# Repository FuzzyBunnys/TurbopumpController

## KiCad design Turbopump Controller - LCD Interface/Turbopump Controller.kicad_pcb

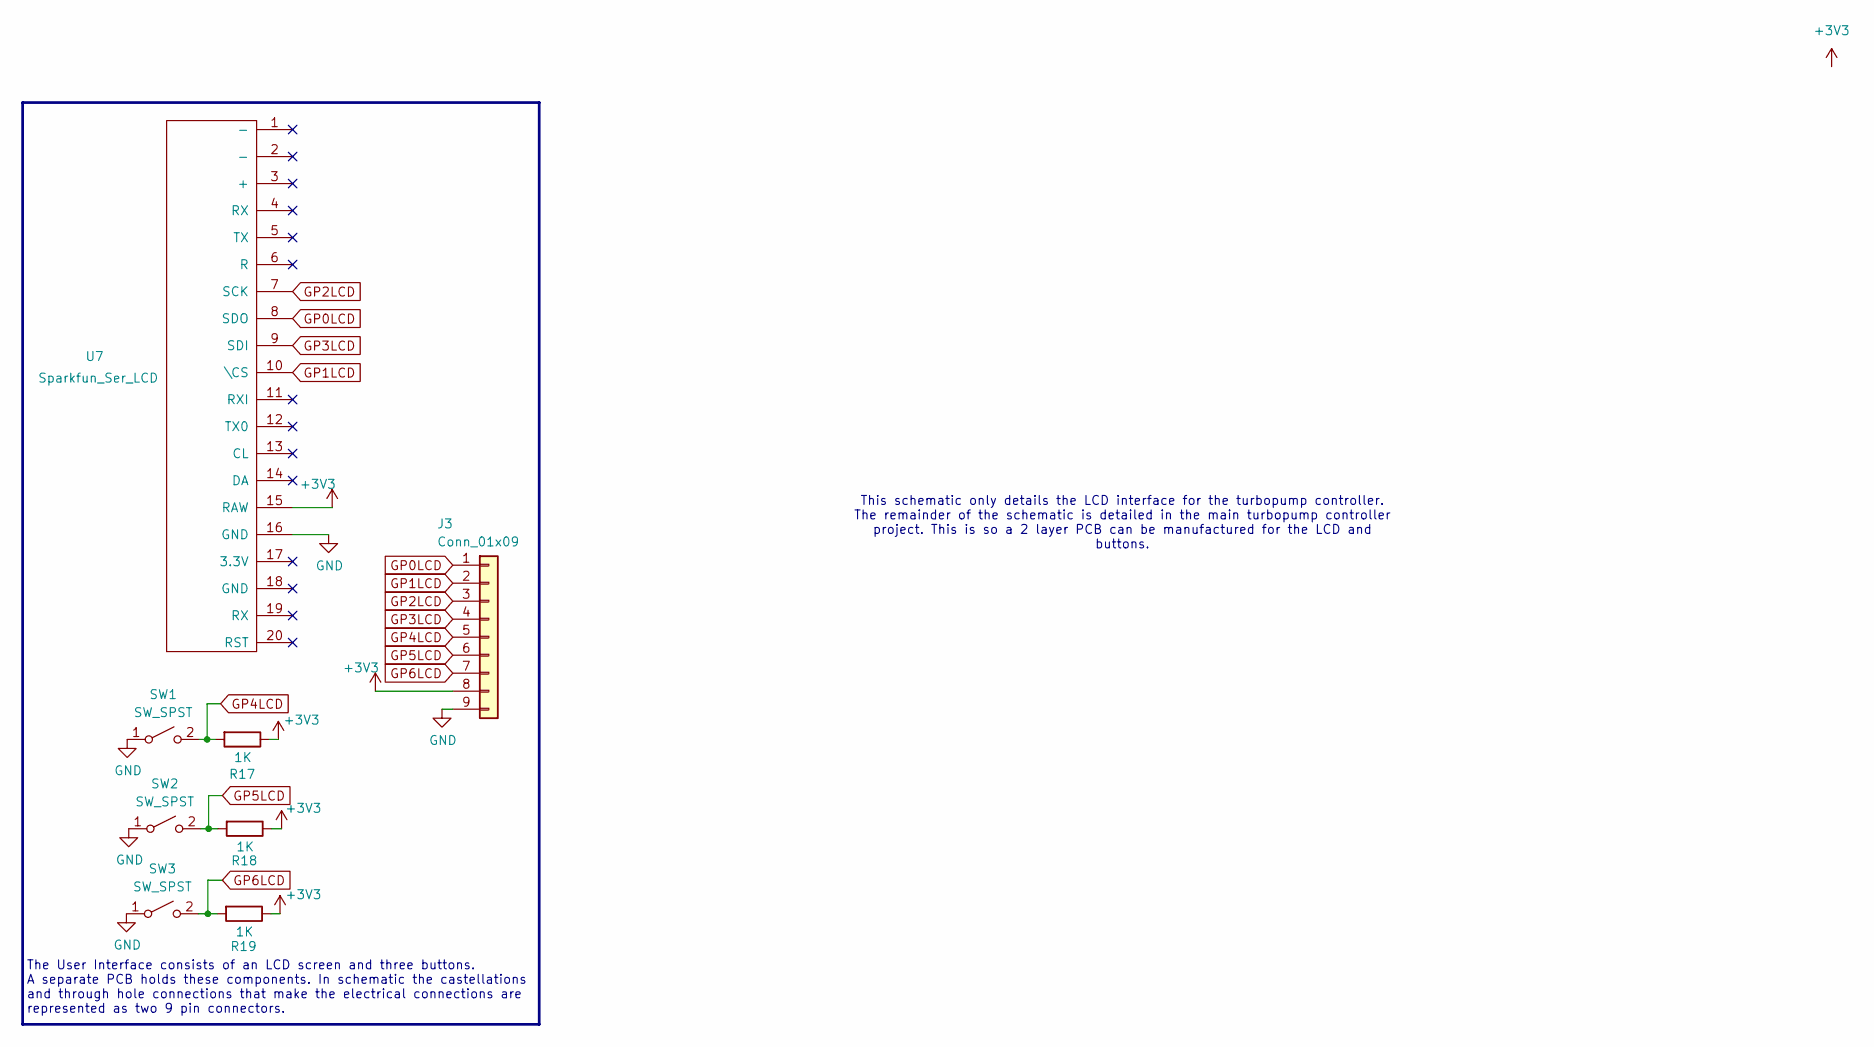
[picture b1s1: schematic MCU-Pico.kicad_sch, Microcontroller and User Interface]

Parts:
J3: Conn_01x09; Castellated_Tpump_Connector
R17, R18, R19: 1K; R_0603_1608Metric
SW1, SW2, SW3: SW_SPST; TL2233 Series Pushbutton Switch
U7: Sparkfun_Ser_LCD; LCD-16X2

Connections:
+3V3: J3.8, R17.1, R18.1, R19.1, U7.15 (RAW)
GND: J3.9, SW1.1 (A), SW2.1 (A), SW3.1 (A), U7.16 (GND)
GP0LCD: J3.1, U7.8 (SDO)
GP1LCD: J3.2, U7.10 (\CS)
GP2LCD: J3.3, U7.7 (SCK)
GP3LCD: J3.4, U7.9 (SDI)
GP4LCD: J3.5, R17.2, SW1.2 (B)
GP5LCD: J3.6, R18.2, SW2.2 (B)
GP6LCD: J3.7, R19.2, SW3.2 (B)

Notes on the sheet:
This schematic only details the LCD interface for the turbopump controller. The remainder of the schematic is detailed in the main turbopump controller project. This is so a 2 layer PCB can be manufactured for the LCD and buttons.
The User Interface consists of an LCD screen and three buttons. A separate PCB holds these components. In schematic the castellations and through hole connections that make the electrical connections are represented as two 9 pin connectors.

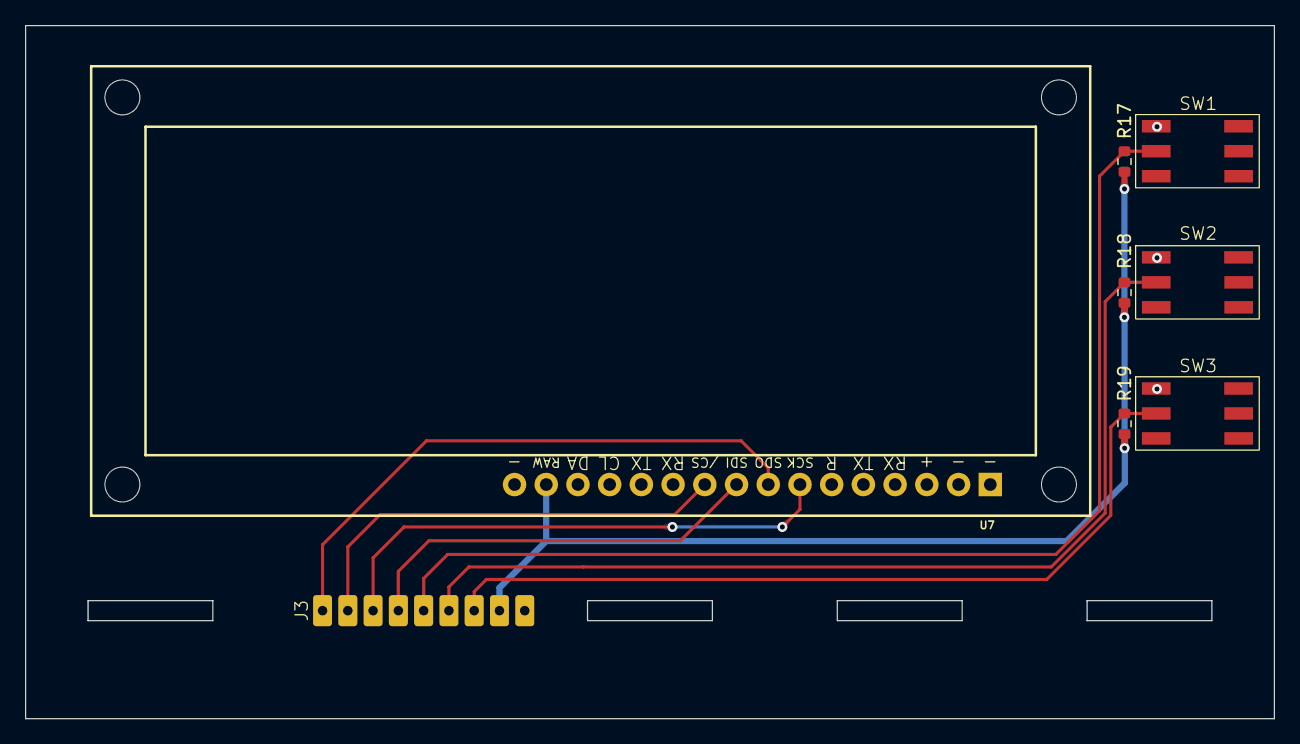
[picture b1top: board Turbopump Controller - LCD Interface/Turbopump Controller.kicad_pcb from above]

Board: 2 copper layers, 100.0 x 55.5 mm, 8 parts (0 on the bottom side), 9 nets.

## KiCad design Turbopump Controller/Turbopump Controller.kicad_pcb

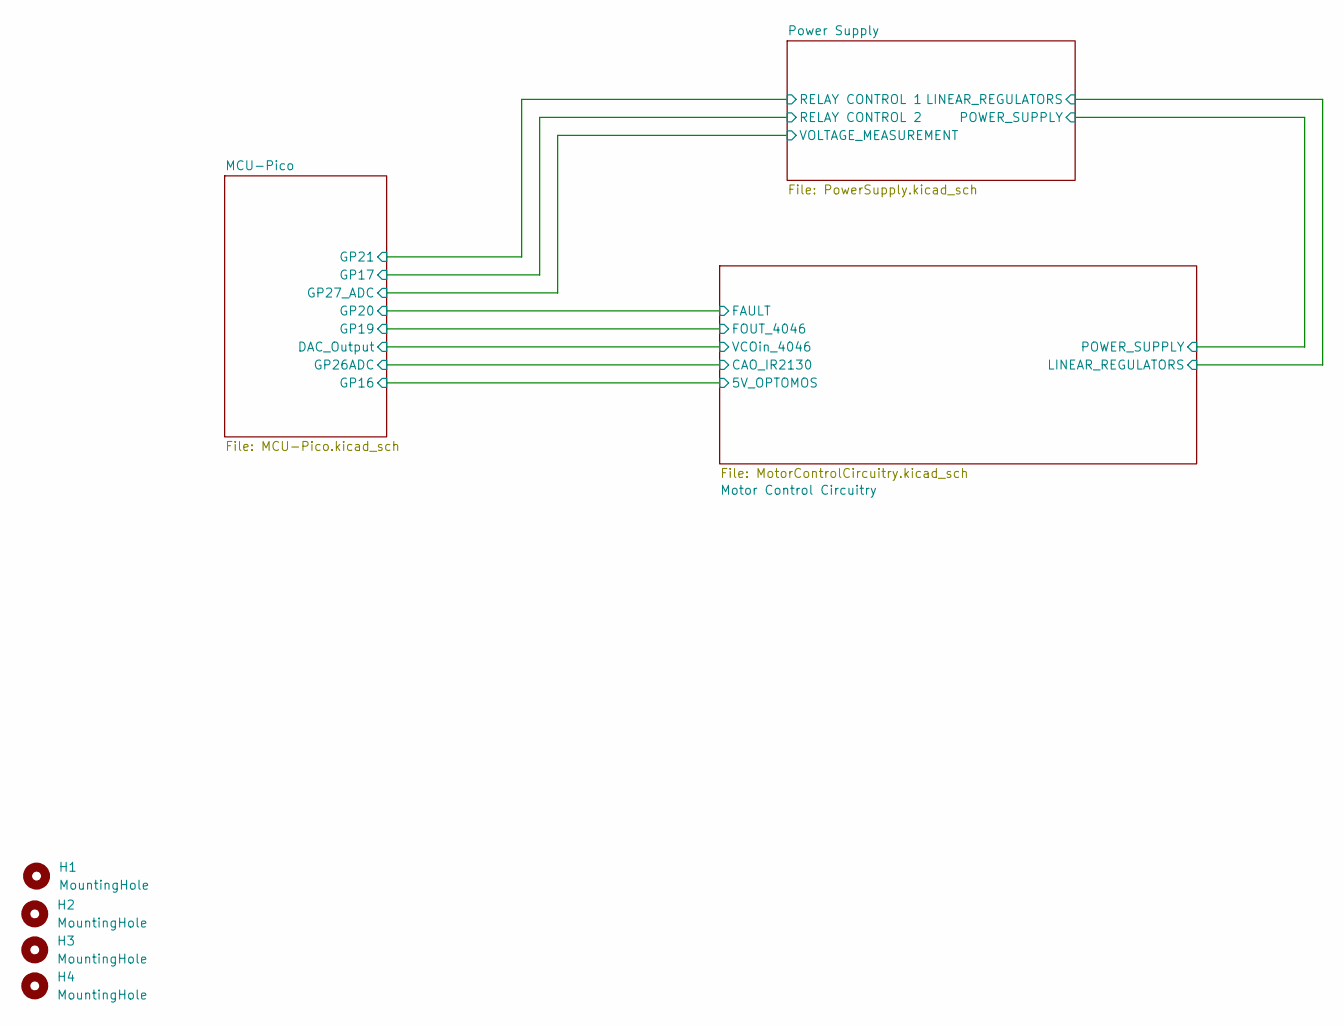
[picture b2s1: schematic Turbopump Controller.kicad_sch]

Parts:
H1, H2, H4: MountingHole; MountingHole_3.2mm_M3_Pad_Via
H3: MountingHole; MountingHole_2.2mm_M2_Pad_Via

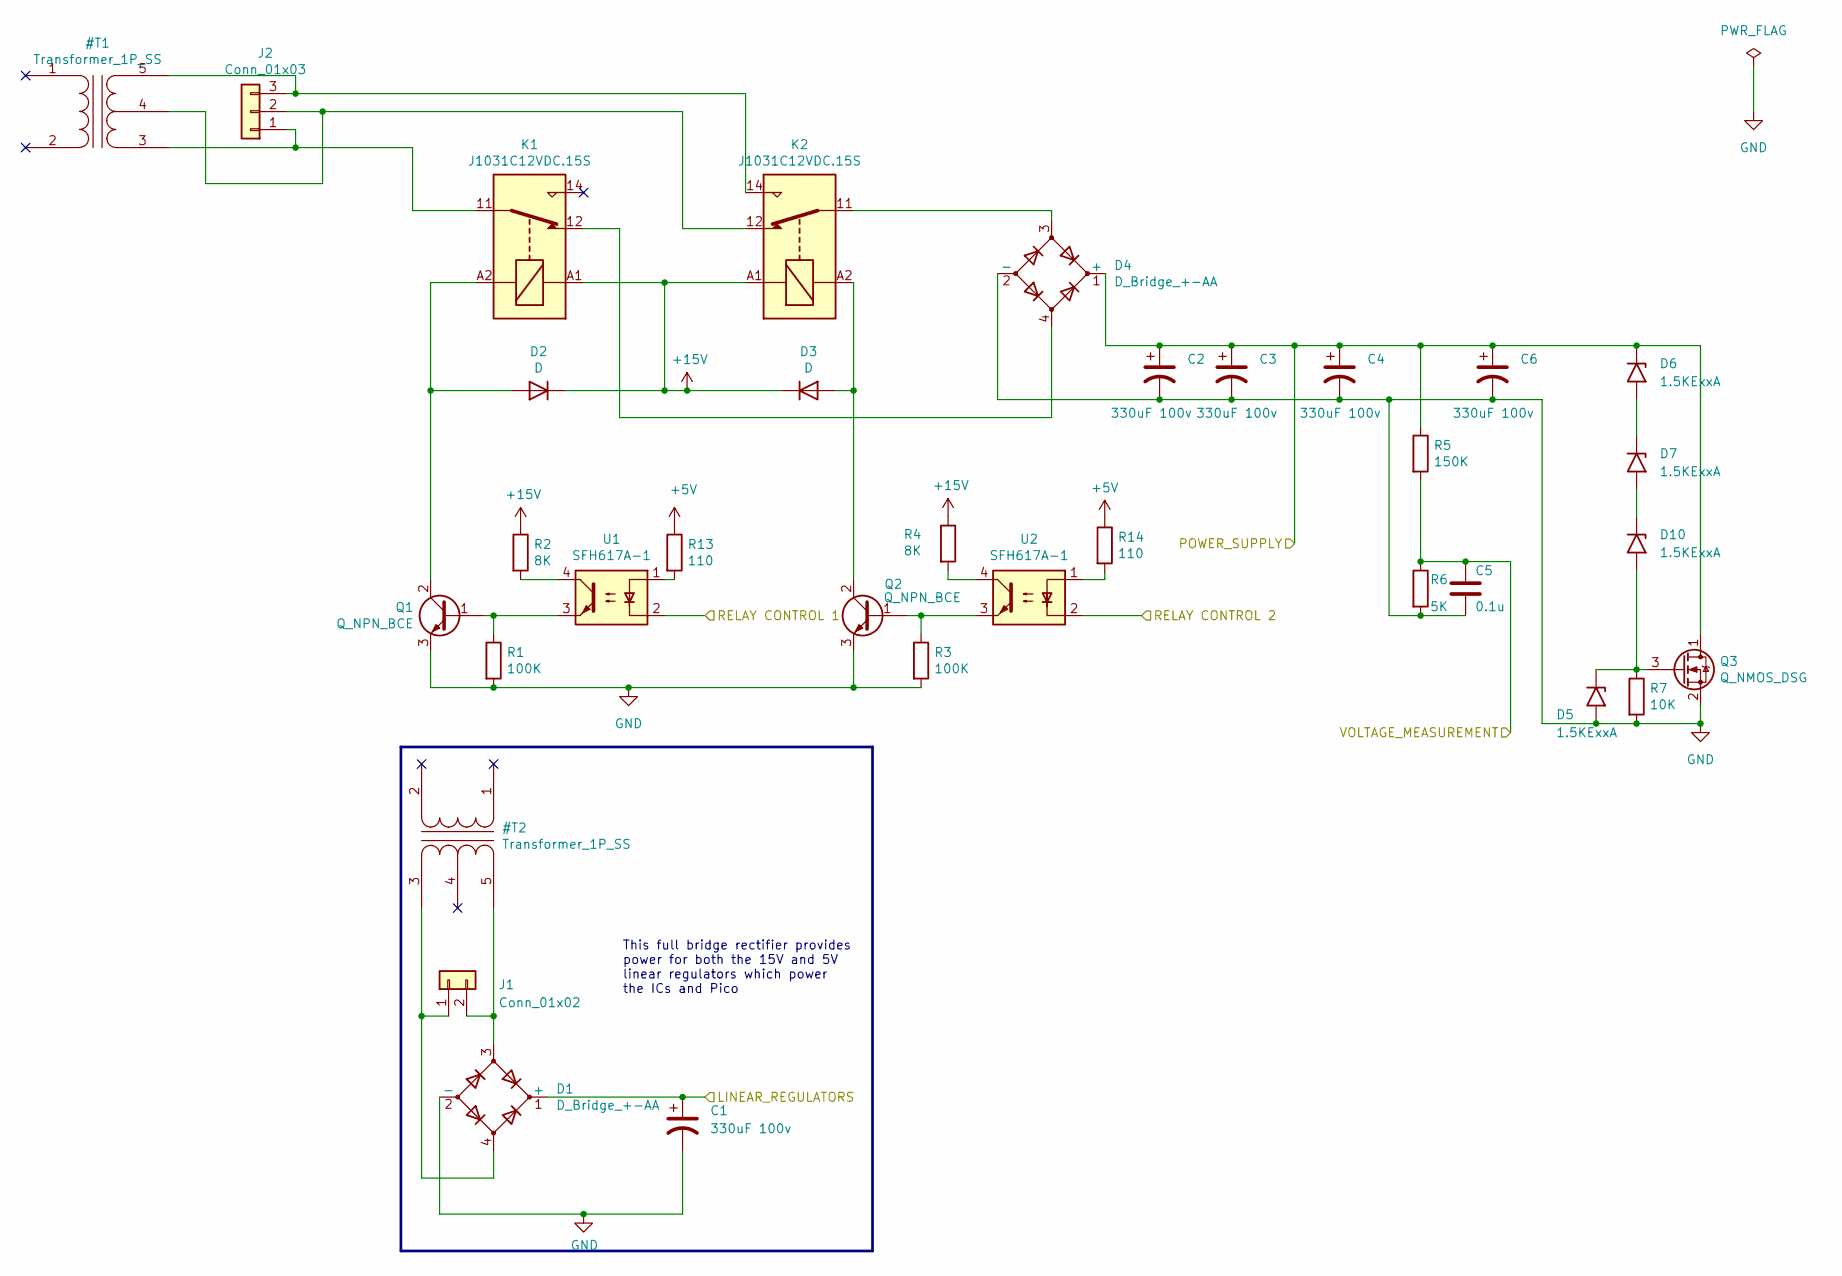
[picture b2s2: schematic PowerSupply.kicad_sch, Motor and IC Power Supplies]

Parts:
C1, C2, C3, C4, C6: 330uF 100v; EEV-FK2A331M
C5: 0.1u; C_0603_1608Metric
D1: D_Bridge_+-AA; KMB25S
D2, D3: D; D_SOD-323F
D4: D_Bridge_+-AA; RDBF32-13
D5, D10: 1.5KExxA; D_SMC_Modified
D6, D7: 1.5KExxA; D_SMB_Modified
J1: Conn_01x02; TerminalBlock_bornier-2_P5.08mm
J2: Conn_01x03; TerminalBlock_bornier-3_P5.08mm
K1, K2: J1031C12VDC.15S; Relay_SPDT_HsinDa_Y14
Q1, Q2: Q_NPN_BCE; SOT-23
Q3: Q_NMOS_DSG; DMTH10H003SPSW-13
R1, R3: 100K; R_0603_1608Metric
R2, R4: 8K; R_0603_1608Metric
R5: 150K; R_0805_2012Metric
R6: 5K; R_0805_2012Metric
R7: 10K; R_0805_2012Metric
R13, R14: 110; R_0603_1608Metric
U1, U2: SFH617A-1; 4-SMD Gullwing

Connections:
+5V: R13.1, R14.1; also elsewhere on the board
+15V: D2.1 (K), D3.1 (K), K1.A1, K2.A1, R2.1, R4.1; also elsewhere on the board
/MCU-Pico/GP17: U2.2; also elsewhere on the board
/MCU-Pico/GP21: U1.2; also elsewhere on the board
/MCU-Pico/GP27_ADC: C5.1, R5.2, R6.1; also elsewhere on the board
/Motor Control Circuitry/LINEAR_REGULATORS: C1.1, D1.1 (+); also elsewhere on the board
/Motor Control Circuitry/POWER_SUPPLY: C2.1, C3.1, C4.1, C6.1, D4.1 (+), D6.1 (A1), Q3.1 (D), R5.1; also elsewhere on the board
GND: C1.2, C2.2, C3.2, C4.2, C5.2, C6.2, D1.2 (-), D4.2 (-), D5.2 (A2), Q1.3 (E), Q2.3 (E), Q3.2 (S), R1.2, R3.2, R6.2, R7.2; also elsewhere on the board
unnamed: D2.2 (A), K1.A2, Q1.2 (C)
unnamed: D3.2 (A), K2.A2, Q2.2 (C)
unnamed: D4.3, K2.11
unnamed: D4.4, K1.12
unnamed: D6.2 (A2), D7.1 (A1)
unnamed: D7.2 (A2), D10.1 (A1)
unnamed: D5.1 (A1), D10.2 (A2), Q3.3 (G), R7.1
unnamed: Q1.1 (B), R1.1, U1.3
unnamed: Q2.1 (B), R3.1, U2.3
unnamed: R2.2, U1.4
unnamed: R4.2, U2.4
unnamed: R13.2, U1.1
unnamed: R14.2, U2.1

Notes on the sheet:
This full bridge rectifier provides power for both the 15V and 5V linear regulators which power the ICs and Pico

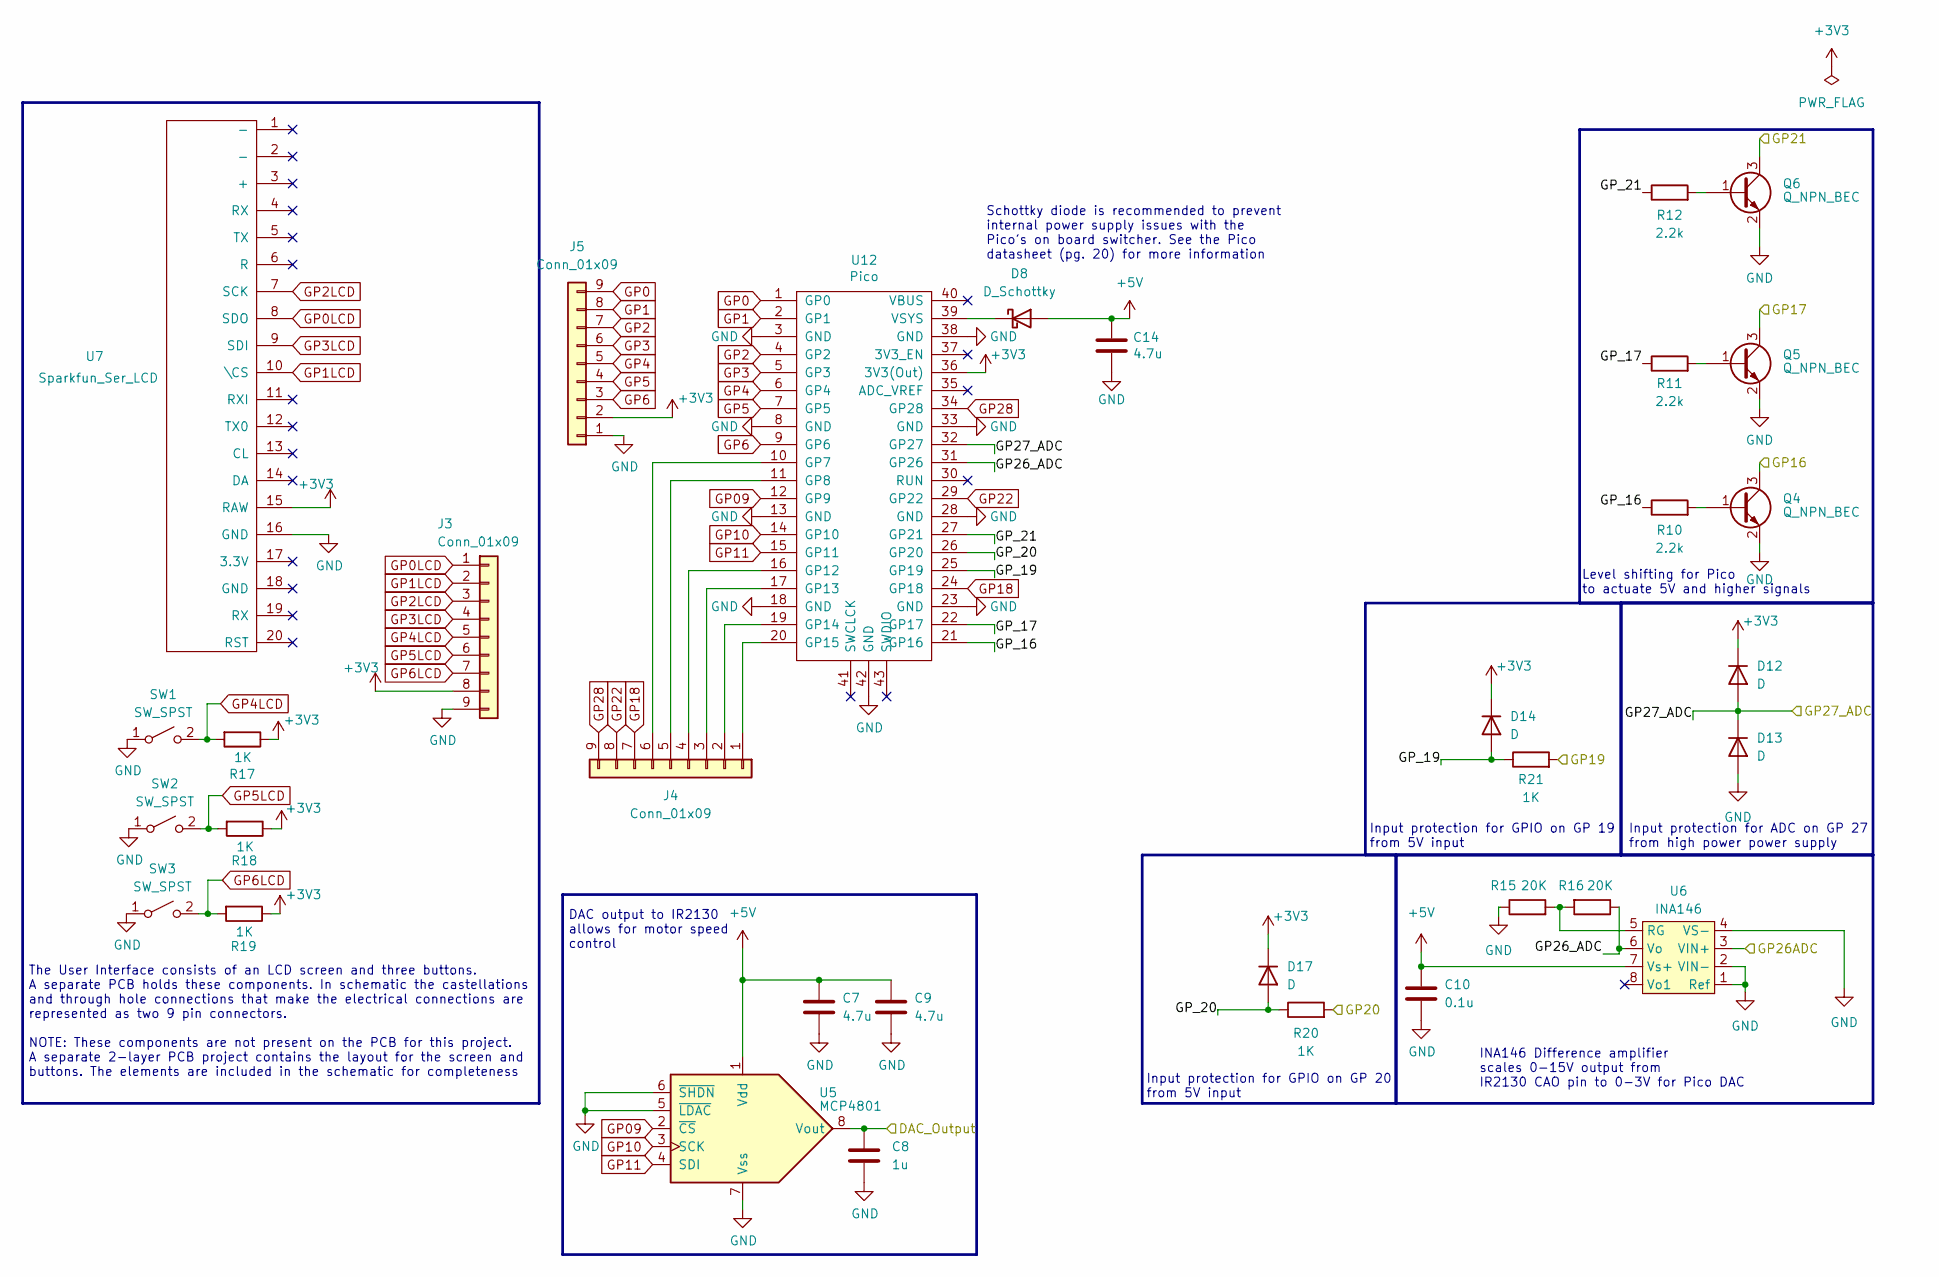
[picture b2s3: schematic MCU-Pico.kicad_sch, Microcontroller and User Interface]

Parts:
C7, C9, C14: 4.7u; C_0603_1608Metric
C8: 1u; C_0603_1608Metric
C10: 0.1u; C_0603_1608Metric
D8: D_Schottky; D_SOD-123F
D12, D13, D14, D17: D; D_SOD-882
J3, J5: Conn_01x09; Castellated_Tpump_Connector
J4: Conn_01x09; PinSocket_1x09_P2.54mm_Vertical
Q4, Q5, Q6: Q_NPN_BEC; TSOT-23
R10, R11, R12: 2.2k; R_0603_1608Metric
R15, R16: 20K; R_0603_1608Metric
R17, R18, R19, R20, R21: 1K; R_0603_1608Metric
SW1, SW2, SW3: SW_SPST; TL2233 Series Pushbutton Switch
U5: MCP4801; DFN-8-1EP_3x2mm_P0.5mm_EP1.75x1.45mm
U6: INA146; SOIC-8-1EP_3.9x4.9mm_P1.27mm_EP2.29x3mm
U7: Sparkfun_Ser_LCD; LCD-16X2
U12: Pico; RPi_Pico_SMD_TH

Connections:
+3V3: D12.1 (K), D14.1 (K), D17.1 (K), J3.8, J5.2, R17.1, R18.1, R19.1, U7.15 (RAW), U12.36 (3V3(Out))
+5V: C7.1, C9.1, C10.1, C14.1, D8.2 (A), U5.1 (Vdd), U6.7 (Vs+); also elsewhere on the board
/MCU-Pico/DAC_Output: C8.1, U5.8 (Vout); also elsewhere on the board
/MCU-Pico/GP16: Q4.3 (C); also elsewhere on the board
/MCU-Pico/GP17: Q5.3 (C); also elsewhere on the board
/MCU-Pico/GP19: R21.2; also elsewhere on the board
/MCU-Pico/GP20: R20.2; also elsewhere on the board
/MCU-Pico/GP21: Q6.3 (C); also elsewhere on the board
/MCU-Pico/GP26ADC: U6.3 (VIN+); also elsewhere on the board
/MCU-Pico/GP26_ADC: R16.1, U6.6 (Vo), U12.31 (GP26)
/MCU-Pico/GP27_ADC: D12.2 (A), D13.1 (K), U12.32 (GP27); also elsewhere on the board
/MCU-Pico/GP_16: R10.1, U12.21 (GP16)
/MCU-Pico/GP_17: R11.1, U12.22 (GP17)
/MCU-Pico/GP_19: D14.2 (A), R21.1, U12.25 (GP19)
/MCU-Pico/GP_20: D17.2 (A), R20.1, U12.26 (GP20)
/MCU-Pico/GP_21: R12.1, U12.27 (GP21)
GND: C7.2, C8.2, C9.2, C10.2, C14.2, D13.2 (A), J3.9, J5.1, Q4.2 (E), Q5.2 (E), Q6.2 (E), R15.1, SW1.1 (A), SW2.1 (A), SW3.1 (A), U5.5 (~LDAC), U5.6 (~SHDN), U5.7 (Vss), U6.1 (Ref), U6.2 (VIN-), U6.4 (VS-), U7.16 (GND), U12.3 (GND), U12.8 (GND), U12.13 (GND), U12.18 (GND), U12.23 (GND), U12.28 (GND), U12.33 (GND), U12.38 (GND), U12.42 (GND); also elsewhere on the board
GP0: J5.9, U12.1 (GP0)
GP1: J5.8, U12.2 (GP1)
GP2: J5.7, U12.4 (GP2)
GP3: J5.6, U12.5 (GP3)
GP4: J5.5, U12.6 (GP4)
GP5: J5.4, U12.7 (GP5)
GP6: J5.3, U12.9 (GP6)
GP09: U5.2 (~CS), U12.12 (GP9)
GP10: U5.3 (SCK), U12.14 (GP10)
GP11: U5.4 (SDI), U12.15 (GP11)
GP18: J4.7, U12.24 (GP18)
GP22: J4.8, U12.29 (GP22)
GP28: J4.9, U12.34 (GP28)
unnamed: D8.1 (K), U12.39 (VSYS)
unnamed: J3.1, U7.8 (SDO)
unnamed: J3.2, U7.10 (\CS)
unnamed: J3.3, U7.7 (SCK)
unnamed: J3.4, U7.9 (SDI)
unnamed: J3.5, R17.2, SW1.2 (B)
unnamed: J3.6, R18.2, SW2.2 (B)
unnamed: J3.7, R19.2, SW3.2 (B)
unnamed: J4.1, U12.20 (GP15)
unnamed: J4.2, U12.19 (GP14)
unnamed: J4.3, U12.17 (GP13)
unnamed: J4.4, U12.16 (GP12)
unnamed: J4.5, U12.11 (GP8)
unnamed: J4.6, U12.10 (GP7)
unnamed: Q4.1 (B), R10.2
unnamed: Q5.1 (B), R11.2
unnamed: Q6.1 (B), R12.2
unnamed: R15.2, R16.2, U6.5 (RG)

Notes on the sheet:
DAC output to IR2130 allows for motor speed control
INA146 Difference amplifier scales 0-15V output from IR2130 CAO pin to 0-3V for Pico DAC
Schottky diode is recommended to prevent internal power supply issues with the Pico's on board switcher. See the Pico datasheet (pg. 20) for more information
Level shifting for Pico to actuate 5V and higher signals
Input protection for GPIO on GP 19 from 5V input
Input protection for GPIO on GP 20 from 5V input
Input protection for ADC on GP 27 from high power power supply
The User Interface consists of an LCD screen and three buttons. A separate PCB holds these components. In schematic the castellations and through hole connections that make the electrical connections are represented as two 9 pin connectors. NOTE: These components are not present on the PCB for this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

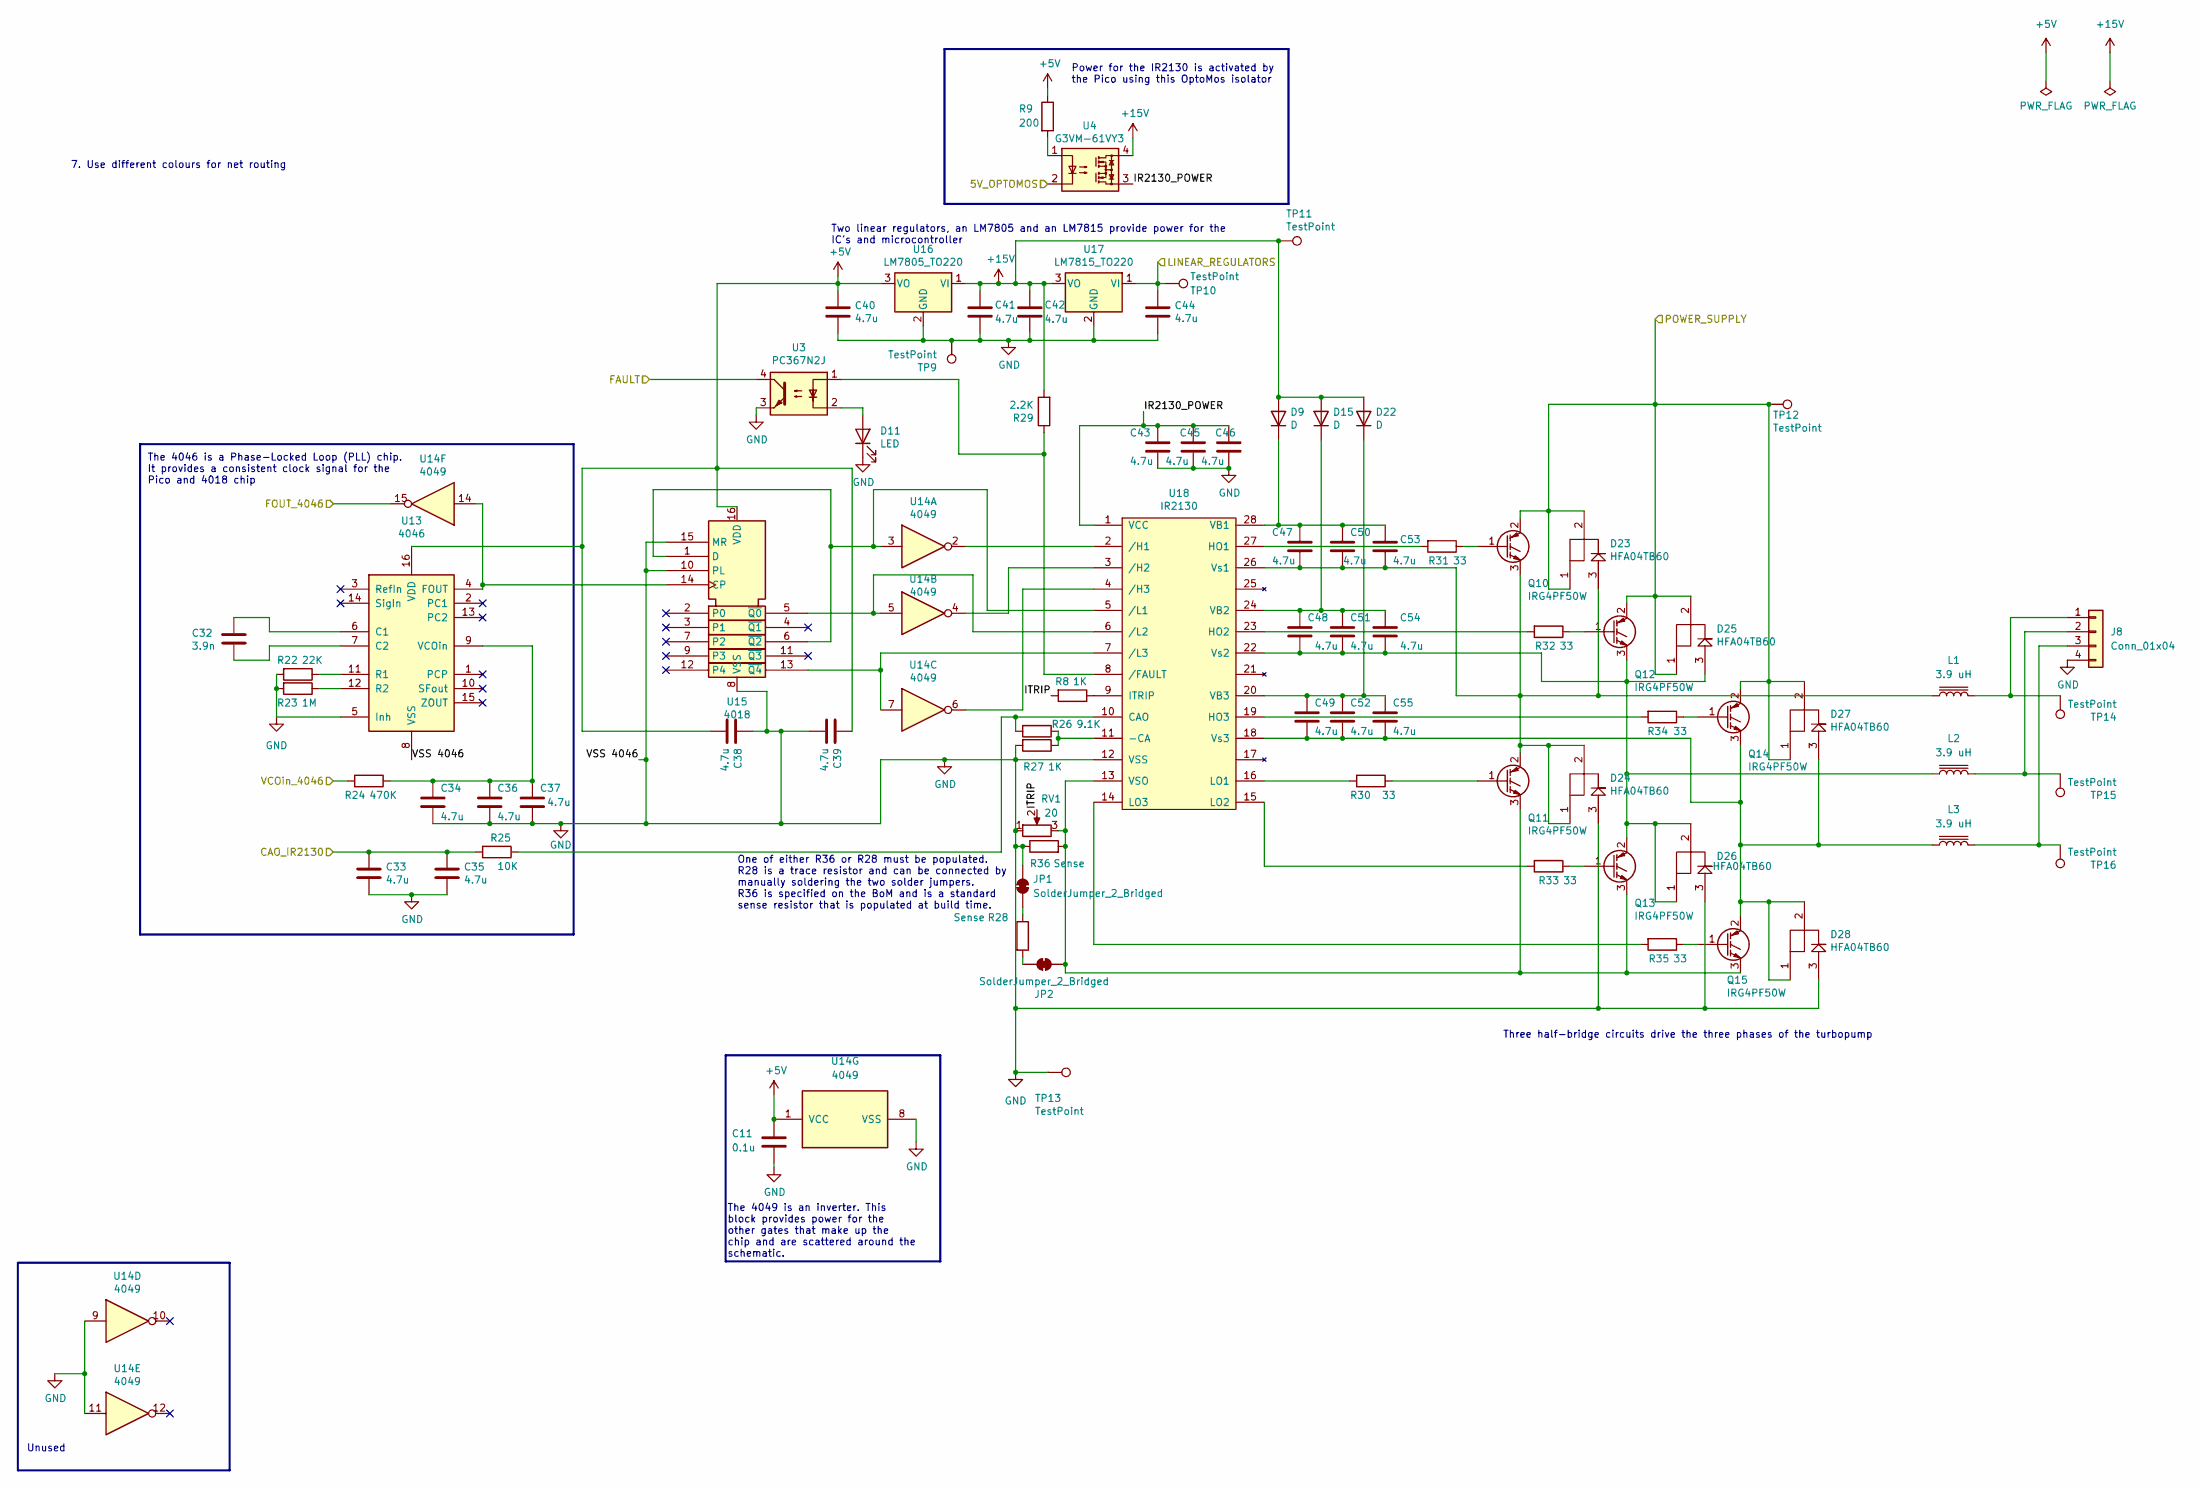
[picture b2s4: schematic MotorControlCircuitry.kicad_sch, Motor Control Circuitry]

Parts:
C11: 0.1u; C_0603_1608Metric
C32: 3.9n; C_0603_1608Metric
C33, C34, C35, C36, C37, C38, C39, C40, C41, C42, C43, C44, C45, C46: 4.7u; C_0603_1608Metric
C47, C48, C49, C50, C51, C52, C53, C54, C55: 4.7u; C_0805_2012Metric
D9, D15, D22: D; D_SMA
D11: LED; LED_0603_1608Metric
D23, D24, D25, D26, D27, D28: HFA04TB60; TO-263-2
J8: Conn_01x04; TerminalBlock_bornier-4_P5.08mm
JP1, JP2: SolderJumper_2_Bridged; SolderJumper-2_P1.3mm_Open_RoundedPad1.0x1.5mm
L1, L2, L3: 3.9 uH; PA4334.392NLT
Q10, Q11, Q12, Q13, Q14, Q15: IRG4PF50W; TO-252-3_TabPin2
R8, R27: 1K; R_0603_1608Metric
R9: 200; R_0603_1608Metric
R22: 22K; R_0603_1608Metric
R23: 1M; R_0603_1608Metric
R24: 470K; R_0603_1608Metric
R25: 10K; R_0603_1608Metric
R26: 9.1K; R_0603_1608Metric
R28: Sense; Shunt_Res
R29: 2.2K; R_0603_1608Metric
R30, R31, R32, R33, R34, R35: 33; R_0603_1608Metric
R36: Sense; R_2512_6332Metric
RV1: 20; 3361P-1-200GLF
TP9, TP10, TP11, TP12, TP13, TP14, TP15, TP16: TestPoint; TestPoint_Pad_D1.0mm
U3: PC367N2J; PC367NJ0000F
U4: G3VM-61VY3; SO-4_4.4x4.3mm_P2.54mm
U13: 4046; HTSSOP-16-1EP_4.4x5mm_P0.65mm_EP3.4x5mm_Mask2.46x2.31mm
U14: 4049; SOIC-16_3.9x9.9mm_P1.27mm
U15: 4018; SOIC-16_3.9x9.9mm_P1.27mm
U16: LM7805_TO220; SOT-223
U17: LM7815_TO220; TO-263-3_TabPin2
U18: IR2130; SOIC-28W_7.5x18.7mm_P1.27mm

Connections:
+5V: C11.1, C38.2, C39.1, C40.1, R9.1, U13.16 (VDD), U14.1 (VCC), U15.16 (VDD), U16.3 (VO); also elsewhere on the board
+15V: C41.1, C42.1, D9.2 (A), D15.2 (A), D22.2 (A), R29.2, TP11.1, U4.4, U16.1 (VI), U17.3 (VO); also elsewhere on the board
/MCU-Pico/DAC_Output: R24.2; also elsewhere on the board
/MCU-Pico/GP16: U4.2; also elsewhere on the board
/MCU-Pico/GP19: U14.15; also elsewhere on the board
/MCU-Pico/GP20: U3.4; also elsewhere on the board
/MCU-Pico/GP26ADC: C33.1, C35.1, R25.2; also elsewhere on the board
/Motor Control Circuitry/IR2130_POWER: C43.1, C45.1, C46.1, U4.3, U18.1 (VCC)
/Motor Control Circuitry/ITRIP: R8.2, RV1.2
/Motor Control Circuitry/LINEAR_REGULATORS: C44.1, TP10.1, U17.1 (VI); also elsewhere on the board
/Motor Control Circuitry/POWER_SUPPLY: D23.1, D23.2, D25.1, D25.2, D27.1, D27.2, Q10.2 (C), Q12.2 (C), Q14.2 (C), TP12.1; also elsewhere on the board
GND: C11.2, C33.2, C34.2, C35.2, C36.2, C37.2, C38.1, C39.2, C40.2, C41.2, C42.2, C43.2, C44.2, C45.2, C46.2, D11.1 (K), D24.3, D26.3, D28.3, J8.4, JP1.2 (B), R22.2, R23.2, R27.2, R36.1, RV1.1, TP9.1, TP13.1, U3.3, U13.5 (Inh), U13.8 (VSS), U14.8 (VSS), U14.9, U14.11, U15.8 (VSS), U15.10 (PL), U15.15 (MR), U16.2 (GND), U17.2 (GND), U18.12 (VSS); also elsewhere on the board
unnamed: C47.1, C50.1, C53.1, D9.1 (K), U18.28 (VB1)
unnamed: D11.2 (A), U3.2
unnamed: C48.1, C51.1, C54.1, D15.1 (K), U18.24 (VB2)
unnamed: C49.1, C52.1, C55.1, D22.1 (K), U18.20 (VB3)
unnamed: J8.1, L1.2, TP14.1
unnamed: J8.2, L2.2, TP15.1
unnamed: J8.3, L3.2, TP16.1
unnamed: JP1.1 (A), R28.1
unnamed: JP2.1 (A), R28.2
unnamed: JP2.2 (B), Q11.3 (E), Q13.3 (E), Q15.3 (E), R36.2, RV1.3, U18.13 (VSO)
unnamed: C47.2, C50.2, C53.2, D23.3, D24.1, D24.2, L1.1, Q10.3 (E), Q11.2 (C), U18.26 (Vs1)
unnamed: Q10.1 (G), R31.1
unnamed: Q11.1 (G), R30.1
unnamed: C48.2, C51.2, C54.2, D25.3, D26.1, D26.2, L2.1, Q12.3 (E), Q13.2 (C), U18.22 (Vs2)
unnamed: Q12.1 (G), R32.1
unnamed: Q13.1 (G), R33.1
unnamed: C49.2, C52.2, C55.2, D27.3, D28.1, D28.2, L3.1, Q14.3 (E), Q15.2 (C), U18.18 (Vs3)
unnamed: Q14.1 (G), R34.1
unnamed: Q15.1 (G), R35.1
unnamed: R9.2, U4.1
unnamed: C32.1, U13.6 (C1)
unnamed: C32.2, U13.7 (C2)
unnamed: U13.4 (FOUT), U14.14, U15.14 (CP)
unnamed: R22.1, U13.11 (R1)
unnamed: R23.1, U13.12 (R2)
unnamed: C34.1, C36.1, C37.1, R24.1, U13.9 (VCOin)
unnamed: U14.3, U15.1 (D), U15.6 (~Q2), U18.5 (/L1)
unnamed: U14.5, U15.5 (~Q0), U18.6 (/L2)
unnamed: U14.7, U15.13 (~Q4), U18.7 (/L3)
unnamed: R26.1, R27.1, U18.11 (-CA)
unnamed: R25.1, R26.2, U18.10 (CAO)
unnamed: R31.2, U18.27 (HO1)
unnamed: R32.2, U18.23 (HO2)
unnamed: R34.2, U18.19 (HO3)
unnamed: R8.1, U18.9 (ITRIP)
unnamed: R30.2, U18.16 (LO1)
unnamed: R33.2, U18.15 (LO2)
unnamed: R35.2, U18.14 (LO3)
unnamed: R29.1, U3.1, U18.8 (/FAULT)
unnamed: U14.2, U18.2 (/H1)
unnamed: U14.4, U18.3 (/H2)
unnamed: U14.6, U18.4 (/H3)

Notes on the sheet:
7. Use different colours for net routing
Unused
Three half-bridge circuits drive the three phases of the turbopump
One of either R36 or R28 must be populated. R28 is a trace resistor and can be connected by manually soldering the two solder jumpers. R36 is specified on the BoM and is a standard sense resistor that is populated at build time.
The 4049 is an inverter. This block provides power for the other gates that make up the chip and are scattered around the schematic.
Two linear regulators, an LM7805 and an LM7815 provide power for the IC's and microcontroller
Power for the IR2130 is activated by the Pico using this OptoMos isolator
The 4046 is a Phase-Locked Loop (PLL) chip. It provides a consistent clock signal for the Pico and 4018 chip

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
